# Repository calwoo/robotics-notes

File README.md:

# robotics-notes
Notes on ROS and other robotics frameworks.

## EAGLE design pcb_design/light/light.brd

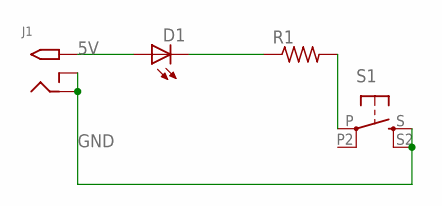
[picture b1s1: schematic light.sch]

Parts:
D1: LED5MM
J1: 2.1MMJACKTHM; PJ-102A
R1: RESISTORTH-1/4W-CARBON; RESAD1160W55L680D260_HS
S1: PUSH-BUTTON-SQUARE; BUTTON-TACTILE-SQUARE-ADAFRUIT1010

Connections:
5V: D1.A, J1.TIP
GND: J1.RING, J1.RING_SW, S1.S, S1.S2 (S1)
unnamed: D1.K (C), R1.1
unnamed: R1.2, S1.P

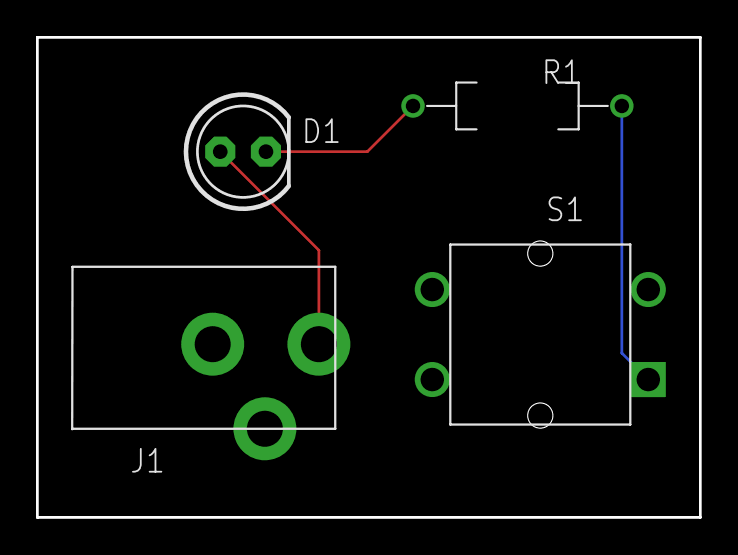
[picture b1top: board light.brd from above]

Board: 2 copper layers, 36.8 x 26.7 mm, 4 parts (0 on the bottom side), 4 nets.

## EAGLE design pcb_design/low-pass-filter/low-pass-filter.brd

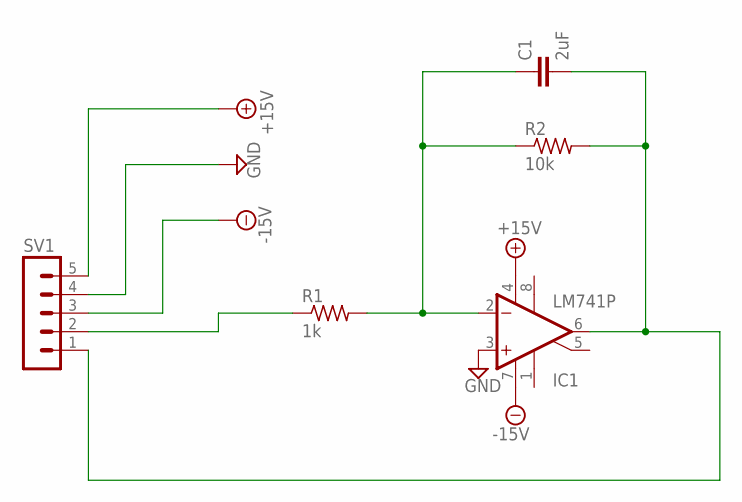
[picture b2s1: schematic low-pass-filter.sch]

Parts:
C1: 2uF; C0603
IC1: LM741P; DIL08
R1: 1k; R0603
R2: 10k; R0603
SV1: MA05-1

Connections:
+15V: IC1.4 (V-), SV1.5
-15V: IC1.7 (V+), SV1.3
GND: IC1.3 (+IN), SV1.4
unnamed: C1.1, IC1.2 (-IN), R1.2, R2.1
unnamed: C1.2, IC1.6 (OUT), R2.2, SV1.1
unnamed: R1.1, SV1.2

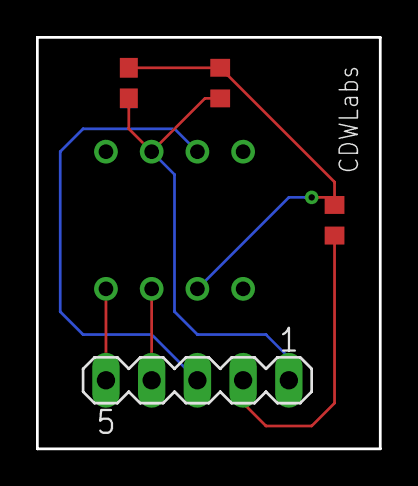
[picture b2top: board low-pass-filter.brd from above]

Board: 2 copper layers, 19.1 x 22.9 mm, 5 parts (1 on the bottom side), 6 nets.

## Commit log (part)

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2022-09-21 add lab4 on pid control
2022-09-22 skibot motion done
2022-09-23 add ros2 service to skibot
2022-09-23 add launch script to skibot proj
2022-09-23 make pa01 launchable
2022-09-23 finish numpy lab
2022-09-23 complete kinematics hw
2022-10-02 start coursera colorado course on embedded systems
2022-10-02 finish coursera assignment 1
2022-10-03 finish assignment 2
2022-10-04 work on assignment 1 of mit 6.096
2022-10-04 finish assignment 1
2022-10-04 halfway done with assignment 2
2022-10-05 halfway through assignment 3
2022-10-14 working through samek's embedded prog course
2022-10-14 finish lesson 1 of quantum leaps course
2022-10-14 blinking an led on the t4mc123gxl!
2022-10-14 finish lesson 5 on the volatile keyword
2022-10-14 working on more lessons
2022-10-15 working through embedded course
2022-10-16 working led switch using interrupts on tm4c launchpad
2022-10-17 start learning pcb design; add low-pass-filter
2022-10-18 learning how to create custom components for eagle
2022-10-18 playing around with tinyzero with ee107
2022-10-19 finish lab on charlieplexing and timers using tinyzero
2022-10-21 implement i2c for bma250 accelerometer on tinyzero
2022-10-25 add kohonen self organizing map implementation
2022-10-28 implement hopfield net
2022-10-28 implement kanerva's sparse distributed memory
2022-10-29 working on umaryland course on rust
2022-10-29 working through rust snake game
2022-10-30 finish snake game in rust
2022-10-31 working through part 1 of helsinki devops docker course
2022-10-31 start umd assignment 3 rust
2022-10-31 working through part 2
2022-11-01 add base ros2 docker image
2022-11-01 playing with ros2 docker vscode workspace env
2022-11-01 start learning ros2 nodes
2022-12-07 finishing topics in ros2
2023-07-02 update docker setup for ros2 to humble and novnc
2023-07-03 going through ros2 course
2023-07-03 start turtlesim catcher project
2023-07-03 attach spawn client for turtles
2023-07-03 finish spawner node
2023-07-03 work on controller; add launch for turtlesim project
2023-07-04 finish turtlesim project
2023-07-04 add skeleta of utoronto project 2
2023-07-08 working on kinematics project
2023-07-08 build diff drive interface package
2023-07-09 finish kinematics practice
2023-07-09 pid control tutorial
